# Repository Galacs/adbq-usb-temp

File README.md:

# ADBQ USB temperature sensor

ESP32-S3 based temperature USB-C compact sensor board made to test small step-down power supply design, i2c ambient temperature sensors, led segment displays and custom class USB peripherals.

## IC List

- ESP32-S3 (Main MCU)
- 2x TMP117 (I2C temperature sensor)
- TPS6282 (Low Iq buck converter)
- 2450AT18A100E (2.45GHz Ceramic chip antenna)
- XL-SB2301SRWC (SMD 3 digit segment display)

## Top preview

## Preview 3d render

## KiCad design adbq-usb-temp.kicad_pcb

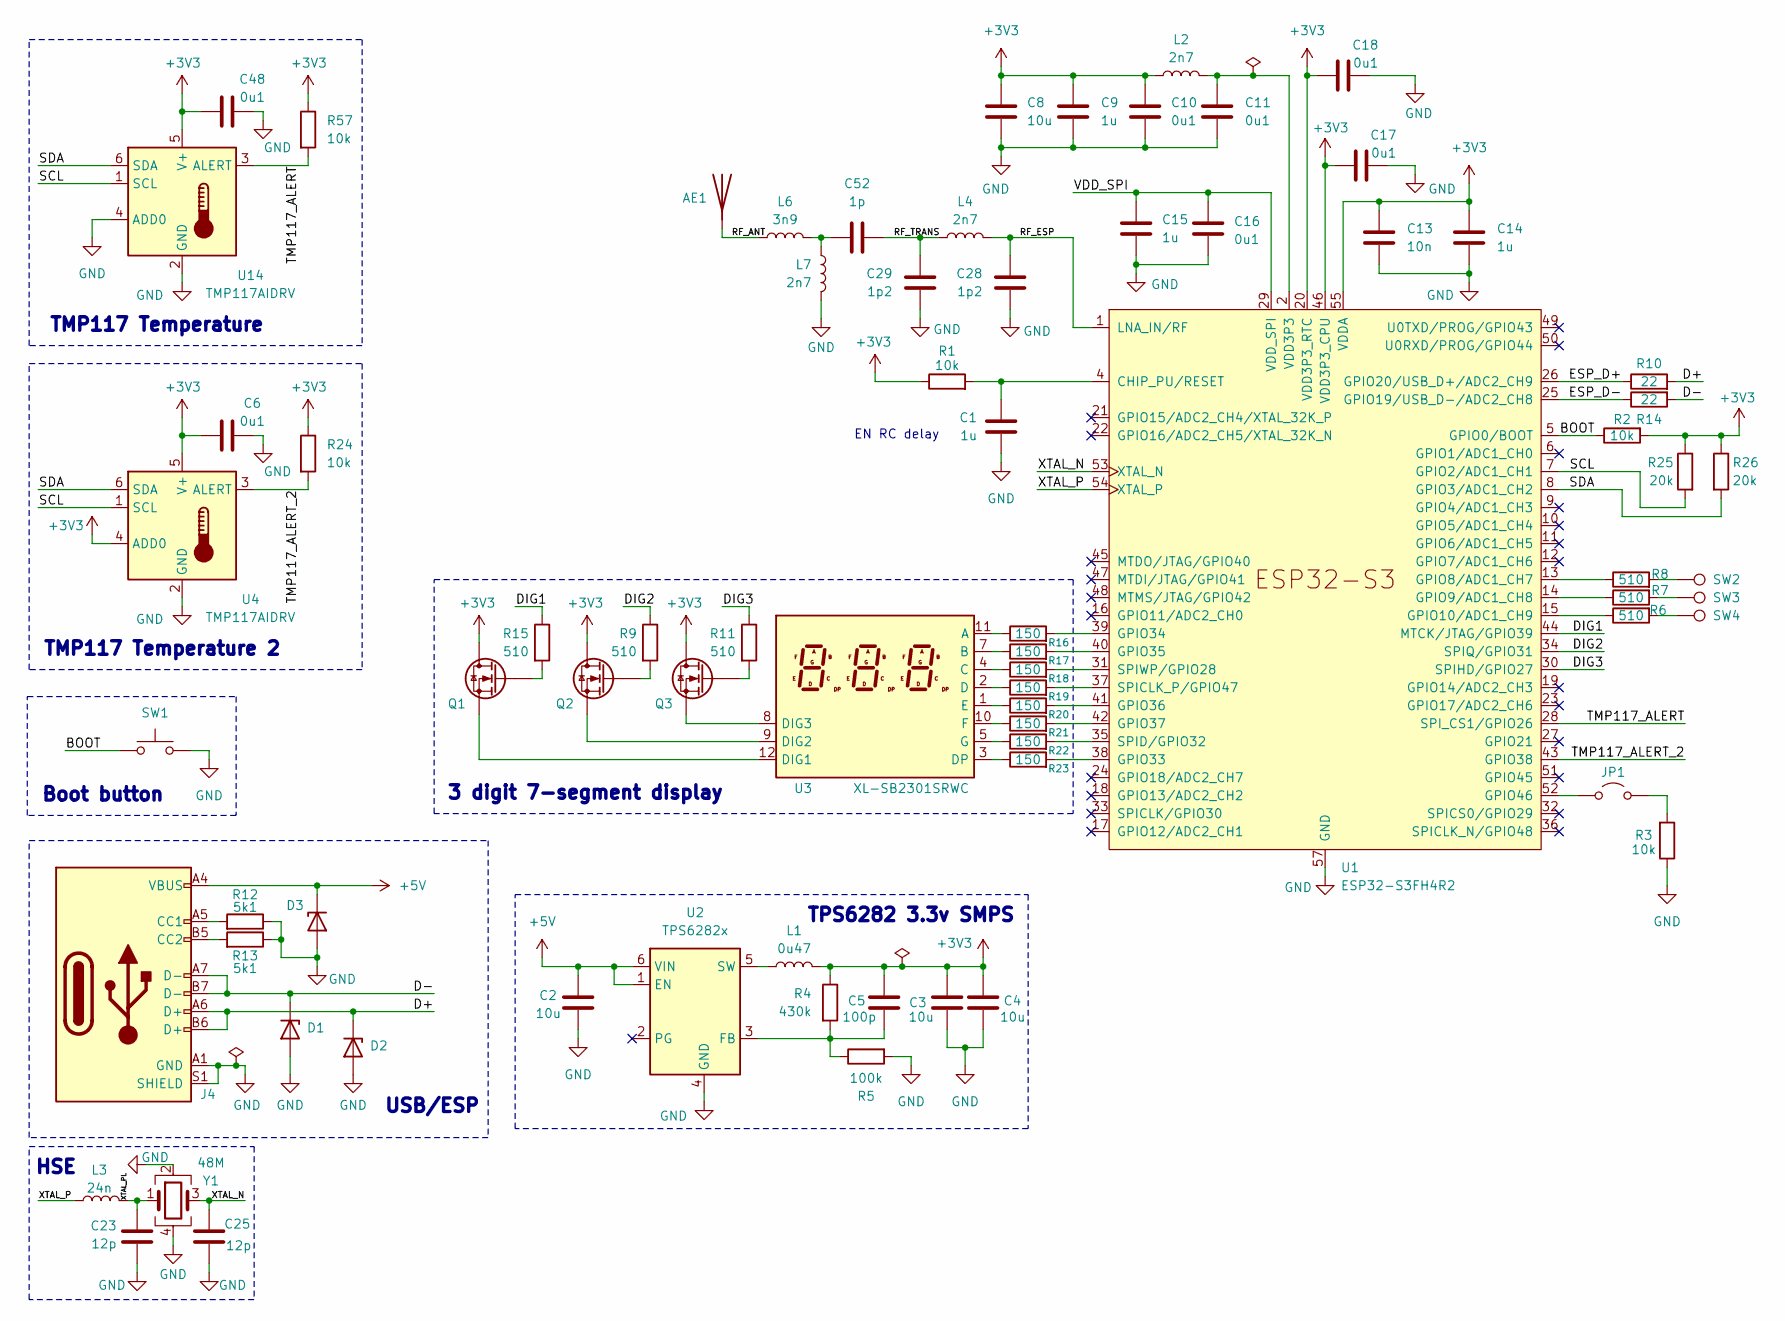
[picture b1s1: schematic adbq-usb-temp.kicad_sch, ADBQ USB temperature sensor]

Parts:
AE1: Antenna; Johanson_2450AT18x100; Manufacturer Part Number 2450AT18A100E; JLCPCB Part # C89334
C1, C9, C14, C15: 1u; C_0402_1005Metric; Manufacturer Part Number CL05A105KA5NQNC; JLCPCB Part # C52923
C2: 10u; C_0603_1608Metric; Manufacturer Part Number CL10A106KP8NNNC; JLCPCB Part # C19702
C3, C4, C8: 10u; C_0402_1005Metric; Manufacturer Part Number CL05A106MQ5NUNC; JLCPCB Part # C15525
C5: 100p; C_0402_1005Metric; Manufacturer Part Number 0402CG101J500NT; JLCPCB Part # C1546
C6, C10, C11, C16, C17, C18, C48: 0u1; C_0402_1005Metric; Manufacturer Part Number CL05B104KB54PNC; JLCPCB Part # C307331
C13: 10n; C_0402_1005Metric; Manufacturer Part Number CL05B103KB5NNNC; JLCPCB Part # C15195
C23, C25: 12p; C_0402_1005Metric; Manufacturer Part Number 0402CG120J500NT; JLCPCB Part # C1547
C28, C29: 1p2; C_0402_1005Metric; Manufacturer Part Number GJM1555C1H1R2WB01D; JLCPCB Part # C76899
C52: 1p; C_0402_1005Metric; Manufacturer Part Number 0402CG1R0C500NT; JLCPCB Part # C1550
D1, D2, D3: H5VU10U; Diode_DFN1006; Manufacturer Part Number H5VU10U; JLCPCB Part # C22395519
J4: USB_C_Receptacle_USB2.0_14P; USB_C_Receptacle_HRO_TYPE-C-31-M-12; Manufacturer Part Number TYPE-C16PIN; JLCPCB Part # C393939
JP1: Jumper_2_Open; SolderJumper-2_P1.3mm_Open_RoundedPad1.0x1.5mm
L1: 0u47; TDK_TFM201610ALC; Manufacturer Part Number TFM201610ALC-R47MTAA; JLCPCB Part # C2045043
L2, L4, L7: 2n7; L_0402_1005Metric; Manufacturer Part Number LQG15HS2N7S02D; JLCPCB Part # C77108
L3: 24n; L_0402_1005Metric; Manufacturer Part Number LQW15AN24NG00D; JLCPCB Part # C167472
L6: 3n9; L_0402_1005Metric; Manufacturer Part Number LQG15HS3N9S02D; JLCPCB Part # C77109
Q1, Q2, Q3: Q_NMOS; SOT-323_SC-70; Manufacturer Part Number BSS138W; JLCPCB Part # C28646265
R1, R2, R3, R24, R57: 10k; R_0402_1005Metric; Manufacturer Part Number 0402WGF1002TCE; JLCPCB Part # C25744
R4: 430k; R_0603_1608Metric; Manufacturer Part Number 0603WAF4303T5E; JLCPCB Part # C25969
R5: 100k; R_0402_1005Metric; Manufacturer Part Number 0402WGF1003TCE; JLCPCB Part # C25741
R6, R7, R8, R9, R11, R15: 510; R_0402_1005Metric; Manufacturer Part Number 0402WGF5100TCE; JLCPCB Part # C25123
R10, R14: 22; R_0402_1005Metric; Manufacturer Part Number 0402WGF220JTCE; JLCPCB Part # C25092
R12, R13: 5k1; R_0402_1005Metric; Manufacturer Part Number 0402WGF5101TCE; JLCPCB Part # C25905
R16, R17, R18, R19, R20, R21, R22, R23: 150; R_0402_1005Metric; Manufacturer Part Number 0402WGF1500TCE; JLCPCB Part # C25082
R25, R26: 20k; R_0402_1005Metric; Manufacturer Part Number 0402WGF2002TCE; JLCPCB Part # C25765
SW1: SW_Push; SolderJumper-2_P1.3mm_Open_RoundedPad1.0x1.5mm
SW2, SW3, SW4: TestPoint; TestPoint_Pad_D1.5mm
U1: ESP32-S3FH4R2; QFN-56-1EP_7x7mm_P0.4mm_EP5.6x5.6mm; Manufacturer Part Number ESP32-S3FH4R2; JLCPCB Part # C3013940
U2: TPS6282x; Texas_VSON-6_1.5x1.5mm_P0.5mm_DMQ0006A; Manufacturer Part Number TPS62825DMQR; JLCPCB Part # C2650334
U3: XL-SB2301SRWC
U4, U14: TMP117AIDRV; WSON-6-1EP_2x2mm_P0.65mm_EP1x1.6mm; Manufacturer Part Number TMP117AIDRVR; JLCPCB Part # C699536
Y1: 48M; Crystal_SMD_2016-4Pin_2.0x1.6mm; Manufacturer Part Number R940000096; JLCPCB Part # C7206306

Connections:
+3V3: C3.1, C4.1, C5.1, C6.1, C8.1, C9.1, C10.1, C13.1, C14.1, C17.1, C18.1, C48.1, L1.2, L2.1, Q1.3 (D), Q2.3 (D), Q3.3 (D), R1.1, R2.2, R4.1, R24.1, R25.1, R26.1, R57.1, U1.20 (VDD3P3_RTC), U1.46 (VDD3P3_CPU), U1.55 (VDDA), U1.56 (VDDA), U4.4 (ADD0), U4.5 (V+), U14.5 (V+)
+5V: C2.1, D3.1 (K), J4.A4 (VBUS), J4.A9 (VBUS), J4.B4 (VBUS), J4.B9 (VBUS), U2.1 (EN), U2.6 (VIN)
/BOOT: R2.1, SW1.1, U1.5 (GPIO0/BOOT)
/D+: D2.1 (K), J4.A6 (D+), J4.B6 (D+), R10.2
/D-: D1.1 (K), J4.A7 (D-), J4.B7 (D-), R14.2
/DIG1: R15.1, U1.44 (MTCK/JTAG/GPIO39)
/DIG2: R9.1, U1.34 (SPIQ/GPIO31)
/DIG3: R11.1, U1.30 (SPIHD/GPIO27)
/ESP_D+: R10.1, U1.26 (GPIO20/USB_D+/ADC2_CH9)
/ESP_D-: R14.1, U1.25 (GPIO19/USB_D-/ADC2_CH8)
/RF_ANT: AE1.1 (A), L6.1
/RF_ESP: C28.1, L4.2, U1.1 (LNA_IN/RF)
/RF_TRANS: C29.1, C52.1, L4.1
/SCL: R25.2, U1.7 (GPIO2/ADC1_CH1), U4.1 (SCL), U14.1 (SCL)
/SDA: R26.2, U1.8 (GPIO3/ADC1_CH2), U4.6 (SDA), U14.6 (SDA)
/TMP117_ALERT: R57.2, U1.28 (SPI_CS1/GPIO26), U14.3 (ALERT)
/TMP117_ALERT_2: R24.2, U1.43 (GPIO38), U4.3 (ALERT)
/VDD_SPI: C15.1, C16.1, U1.29 (VDD_SPI)
/XTAL_N: C25.1, U1.53 (XTAL_N), Y1.3
/XTAL_P: L3.1, U1.54 (XTAL_P)
/XTAL_PL: C23.2, L3.2, Y1.1
GND: C1.2, C2.2, C3.2, C4.2, C6.2, C8.2, C9.2, C10.2, C11.2, C13.2, C14.2, C15.2, C16.2, C17.2, C18.2, C23.1, C25.2, C28.2, C29.2, C48.2, D1.2 (A), D2.2 (A), D3.2 (A), J4.A1 (GND), J4.A12 (GND), J4.B1 (GND), J4.B12 (GND), J4.S1 (SHIELD), L7.1, R3.1, R5.2, R12.1, R13.1, SW1.2, U1.57 (GND), U2.4 (GND), U4.2 (GND), U14.2 (GND), U14.4 (ADD0), U14.7, Y1.2, Y1.4
unnamed: C52.2, L6.2, L7.2
unnamed: J4.A5 (CC1), R12.2
unnamed: J4.B5 (CC2), R13.2
unnamed: JP1.1 (A), U1.52 (GPIO46)
unnamed: JP1.2 (B), R3.2
unnamed: Q1.1 (G), R15.2
unnamed: Q1.2 (S), U3.12 (DIG1)
unnamed: Q2.1 (G), R9.2
unnamed: Q2.2 (S), U3.9 (DIG2)
unnamed: Q3.1 (G), R11.2
unnamed: Q3.2 (S), U3.8 (DIG3)
unnamed: R6.2, SW4.1
unnamed: R7.2, SW3.1
unnamed: R8.2, SW2.1
unnamed: C1.1, R1.2, U1.4 (CHIP_PU/RESET)
unnamed: R8.1, U1.13 (GPIO8/ADC1_CH7)
unnamed: R7.1, U1.14 (GPIO9/ADC1_CH8)
unnamed: R6.1, U1.15 (GPIO10/ADC1_CH9)
unnamed: R23.2, U1.38 (GPIO33)
unnamed: R16.2, U1.39 (GPIO34)
unnamed: R17.2, U1.40 (GPIO35)
unnamed: R20.2, U1.41 (GPIO36)
unnamed: R21.2, U1.42 (GPIO37)
unnamed: R19.2, U1.37 (SPICLK_P/GPIO47)
unnamed: R22.2, U1.35 (SPID/GPIO32)
unnamed: R18.2, U1.31 (SPIWP/GPIO28)
unnamed: C5.2, R4.2, R5.1, U2.3 (FB)
unnamed: L1.1, U2.5 (SW)
unnamed: R16.1, U3.11 (A)
unnamed: R17.1, U3.7 (B)
unnamed: R18.1, U3.4 (C)
unnamed: R19.1, U3.2 (D)
unnamed: R23.1, U3.3 (DP)
unnamed: R20.1, U3.1 (E)
unnamed: R21.1, U3.10 (F)
unnamed: R22.1, U3.5 (G)
TMP_PAD_2: U4.7
VDD3P3: C11.1, L2.2, U1.2 (VDD3P3), U1.3 (VDD3P3)

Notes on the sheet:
TMP117 Temperature
USB/ESP
TPS6282 3.3v SMPS
HSE
EN RC delay
TMP117 Temperature 2
Boot button
3 digit 7-segment display

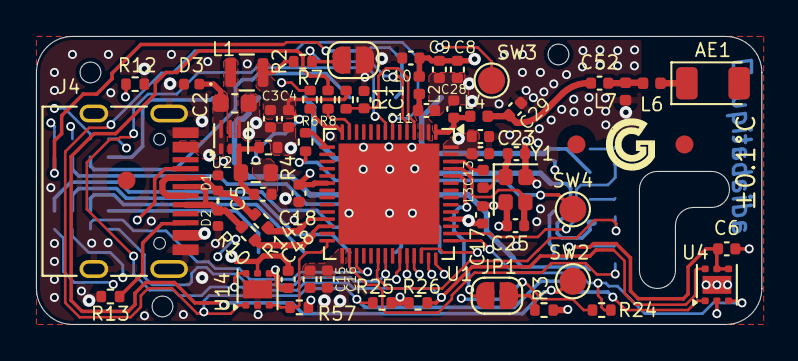
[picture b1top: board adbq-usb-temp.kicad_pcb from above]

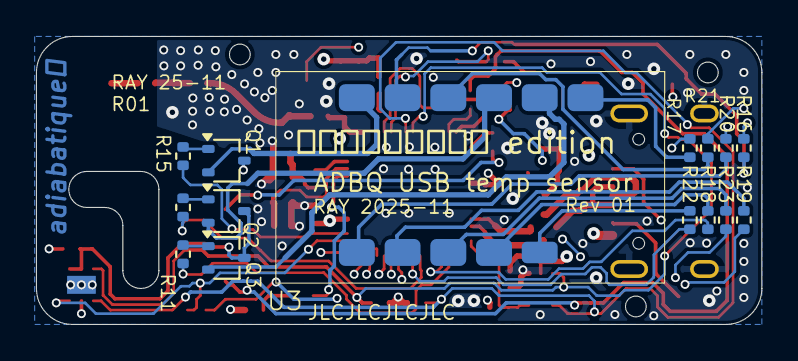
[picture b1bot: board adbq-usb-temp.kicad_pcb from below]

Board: 4 copper layers, 40.3 x 16.0 mm, 74 parts (15 on the bottom side), 59 nets.

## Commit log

2025-10-09 schem: add ESP32-S3FH4R2 symbol
2025-10-09 schem: add ESP32 decoupling caps
2025-10-09 schem: add rf antenna and matching networks
2025-10-09 schem: add HSE crystal
2025-10-09 schem: add usb c connector
2025-10-17 schem: add esp32 en pullup
2025-10-17 schem: add TMP117 temperature sensor
2025-10-23 POC(schem): remove USB-C diode
2025-10-23 POC(schem): replace usb TVS array with TVS diodes
2025-11-14 schem: remove usb 5v capacitor
2025-11-14 schem: add TPS6282 symbol and circuit
2025-11-14 schem: add TPS6282 components values
2025-11-14 schem: add touch inputs
2025-11-14 schem: add 3d digit segment display
2025-11-14 schem: add second TMP117 temperature sensor
2025-11-14 schem: add no connects
2025-11-14 schem: run and fix ERC
2025-11-14 schem: add i2c pullup
2025-11-14 schem: connect TMP117 altert pins to MCU
2025-11-14 schem: add title
2025-11-14 schem: assign footprints
2025-11-14 schem: add part numbers
2025-11-14 pcb: create file
2025-11-14 pcb: import stackup
2025-11-14 schem: update MOSFETs pin numbers
2025-11-14 pcb: import footprints from schematic
2025-11-14 pcb: add missing 3d models
2025-11-14 pcb: inital rough placement
2025-11-14 pcb: layout refinement
2025-11-14 pcb: area reduction
2025-11-14 pcb: add board outline
2025-11-14 pcb: add inner gnd planes
2025-11-14 pcb: add tooling holes
2025-11-14 pcb: add fiducials
2025-11-14 pcb: add gnd vias
2025-11-14 pcb: add rf routing
2025-11-14 pcb: add HSE routing
2025-11-14 pcb: add USB routing
2025-11-14 pcb: add SMPS routing
2025-11-14 pcb: add GPIO46 strapping routing
2025-11-14 pcb: add i2c routing
2025-11-14 pcb: add segment display routing
2025-11-14 pcb: add dril/place origin
2025-11-15 pcb: add TMP117 routing
2025-11-15 pcb: finish USB routing
2025-11-15 pcb: add 3v3 routing
2025-11-15 pcb: add edge TMP117 pad and keepout
2025-11-15 pcb: add TMP117 board cutout
2025-11-15 pcb: add top GND pour
2025-11-15 pcb: add stitching vias
2025-11-15 pcb: clean tracks
2025-11-15 pcb: run and fix DRC
2025-11-15 pcb: clean bottom and top silkscreen
2025-11-15 pcb: add title
2025-11-15 pcb: add bottom silkscreen
2025-11-15 pcb: remove unused internal pads
2025-11-16 pcb: add production files
2025-11-26 schem: update segment display mosfets to correct led polarities
2025-11-26 pcb: fix segment display layout and run ERC
2025-11-26 regenerate production files
2025-11-30 add README.md
2025-11-30 add images to readme
